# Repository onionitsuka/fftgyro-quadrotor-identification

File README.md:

# FFTGYRO quadrotor identification and SITL

三軸姿勢試験台 FFT GYRO を用いたクアッドロータの荷重・推進応答の同定と、
同定モデルを使ったオフラインシミュレーション／PX4 SITL の研究コードです。

解析・同定、収録用ツール、マイコン／Raspberry Pi の実装、PX4 パッチを収録しています。
実験ログ、解析入力 bundle、第三者のソースツリーは含みません。
**データなしで実行できる例は `sim/appendix/`、論文解析の入口は `analysis.py` です。**

## はじめに

Python 3.11 以上を使い、このリポジトリのルートで実行してください。

```sh
python3 -m venv .venv
.venv/bin/python -m pip install -e '.[analysis,hardware,dev]'
.venv/bin/python -m pytest -q
```

Windows PowerShell では最初のコマンドを `py -3 -m venv .venv`、
以降の `.venv/bin/python` を `.\.venv\Scripts\python.exe` に置き換えてください。
Python の数値処理だけなら `hardware` は不要です。全テストには収録系の依存も使います。
PX4・Gazebo・C++ のビルド環境は Python パッケージに含まれません。
対象と既知の制約は [検証範囲](docs/TESTING.md) を参照してください。

## 入口と再現できる範囲

| やりたいこと | 入口 | 追加で必要なもの |
| --- | --- | --- |
| 保存済み係数で飛行例を計算する | [sim/appendix/](sim/appendix/README.md) | Python 依存のみ |
| 荷重を再構成し、モデルを同定・評価する | [analysis.py](analysis.py) | 実験入力 bundle |
| 保存済み結果から図・表を出す | [analysis_output.py](analysis_output.py) | 解析結果ディレクトリ |
| 現用の荷重モデルを PX4 と組み合わせる | [scripts/run_current_px4_sitl.py](scripts/run_current_px4_sitl.py) | 外部 PX4 ビルド、同定係数・機体設定 |
| Gazebo の機体を使う比較を行う | [scripts/run_native_gazebo_sitl.py](scripts/run_native_gazebo_sitl.py) | 外部 PX4/Gazebo、モデル成果物 |
| 収録・同期処理を読む | [src/fftgyro_quad_id/](src/fftgyro_quad_id/) | 実機運用には装置固有の構成が必要 |

付録シミュレーターは共通の簡易制御器を使います。PX4 SITL や実飛行の再現とは別の計算例です。
MoCap の記録飛行を使う過去の採用版比較は、外部の凍結実行環境とログを必要とするため収録していません。

## データなしで試す

```sh
.venv/bin/python sim/appendix/simulate.py --output sim/appendix/results/example
.venv/bin/python sim/appendix/simulate.py --output sim/appendix/results/example --plot-only
```

比較図は `sim/appendix/results/example/comparison.png` に保存されます。
既存の結果を保つため、再計算時は新しい出力先を指定してください。
ブラウザでの操縦例や Windows の手順は [付録の README](sim/appendix/README.md) を参照してください。

## 解析・同定

入力 bundle を用意した場合の例です。入力形式は [解析入力と出力](docs/ANALYSIS.md) に記載しています。
実験データは配布していないため、このコマンドだけで論文の数値結果を再現することはできません。

```sh
.venv/bin/python analysis.py --bundle /path/to/input-bundle --output output/analysis
.venv/bin/python analysis_output.py --input output/analysis --output output/report
```

`--refit` で保存済み構造に対する係数再推定、`--six-axis --refit` で追加 3 軸を含む
同定・評価を実行します。項の再選択や感度解析は明示的なオプションです。
図・表だけを変更する場合は `analysis_output.py` だけを実行してください。

## コードの構成

| パス | 内容 |
| --- | --- |
| `analysis.py`, `analysis_search.py` | 再構成、回帰、候補探索、誤差計算 |
| `analysis_output.py` | 保存済み結果から図・表を出力 |
| `src/fftgyro_quad_id/` | 同期、座標変換、同定、装置通信などの共通実装 |
| `scripts/` | 現行の起動処理とその依存23ファイル。[入口一覧](scripts/README.md) |
| `tests/` | 合成信号、数式の不変条件、通信モック等を使うテスト |
| `configs/` | 設定例とテスト・実装が参照する条件。区分は [設定の扱い](docs/CONFIGURATIONS.md) を参照 |
| `sim/appendix/` | 保存済み係数による単独シミュレーター |
| `onboard_executor/`, `firmware/`, `hardware/` | Pi 実行系、マイコンのコード、回路設計 |
| `protocol/`, `patches/px4/` | MAVLink 定義と外部 PX4 へ適用するパッチ |

既存の import・パス参照を保つため、研究用コードのフォルダ名は維持しています。
`analysis.py` から読み始め、SITL は [スクリプトの入口](scripts/README.md) を参照してください。

## 先行研究

モデルの項選択には、Sun et al.（2019）の前進・後退ステップワイズ回帰を用いています。
F検定の閾値とPSEによる停止条件は、著者らの公開MATLAB実装を参照し、Pythonで計算しています。

- [Sun, de Visser, and Chu (2019), Quadrotor Gray-Box Model Identification from High-Speed Flight Data](https://doi.org/10.2514/1.C035135)
- [著者らのMATLAB参照実装（固定コミット）](https://github.com/SihaoSun/stepwise_regression/tree/b04095ccb9f0e5dcafae43db6ec1a4320cbd0b16/func)

## 比較条件と解釈

- 実験の物理モデル比較は、実測 RPM がある同一標本で行います。欠測を推算 RPM で補いません。
- `measured` と `command_route` は学習・予測で使う RPM の経路です。推算経路の fit に実測 RPM を混ぜません。
- シミュレーション中の RPM は生成値です。実測 RPM と区別してください。
- 全学習データへの一致と条件別検証を分け、独立停止基準とモデル補助基準を分けます。
- 試験台上の荷重一致だけで自由飛行の精度を保証しません。RTS やゼロ位相フィルタはオフライン処理です。

## ライセンスと外部依存

プロジェクト全体のライセンスは未設定です。
外部依存は [docs/DEPENDENCIES.md](docs/DEPENDENCIES.md)、
第三者由来部分の出典とライセンスは [THIRD_PARTY.md](THIRD_PARTY.md) を参照してください。

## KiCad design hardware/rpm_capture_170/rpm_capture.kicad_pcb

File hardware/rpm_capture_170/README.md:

# RPM capture board

KiCad の回路・基板設計と、配置・経路・組立図を生成する補助コードです。
`rpm_capture.kicad_pro` を KiCad で開いてください。

- 設計ソース：`rpm_capture.kicad_sch`、`rpm_capture.kicad_pcb`、`RPM.kicad_sym`。
- 配置情報：`layout.json`。`previous_layout.json` は比較検証に使う前の配置です。
- 生成・検査：`layout_work.py`、`refine_routes.py`、`make_schematic.py`、`verify_and_render.py`、`make_guide.py`。
- SPICE 計算：`receiver_demo.cir`、`run_simulation.py`。
- 図と検査記録：SVG、組立図 HTML、`verification.json`、`erc.rpt`。

生成スクリプトはこのフォルダ内の設計・出力を更新するため、試す場合はコピーを使ってください。
Python の通常テストには含めていません。KiCad／SPICE と描画の実行環境は別途必要です。

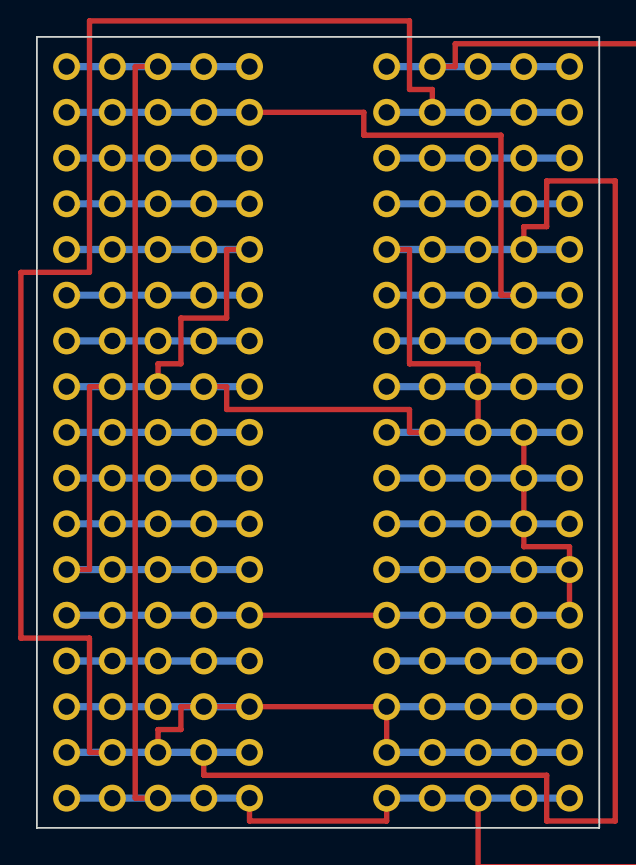
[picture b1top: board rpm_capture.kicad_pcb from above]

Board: 2 copper layers, 31.2 x 43.9 mm, 170 parts (0 on the bottom side), 21 nets.

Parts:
A1: A1
A2: A2
A3: A3
A4: A4
A5: A5
A6: A6
A7: A7
A8: A8
A9: A9
A10: A10
A11: A11
A12: A12
A13: A13
A14: A14
A15: A15
A16: A16
A17: A17
B1: B1
B2: B2
B3: B3
B4: B4
B5: B5
B6: B6
B7: B7
B8: B8
B9: B9
B10: B10
B11: B11
B12: B12
B13: B13
B14: B14
B15: B15
B16: B16
B17: B17
C1: C1
C2: C2
C3: C3
C4: C4
C5: C5
C6: C6
C7: C7
C8: C8
C9: C9
C10: C10
C11: C11
C12: C12
C13: C13
C14: C14
C15: C15
C16: C16
C17: C17
D1: D1
D2: D2
D3: D3
D4: D4
D5: D5
D6: D6
D7: D7
D8: D8
D9: D9
D10: D10
D11: D11
D12: D12
D13: D13
D14: D14
D15: D15
D16: D16
D17: D17
E1: E1
E2: E2
E3: E3
E4: E4
E5: E5
E6: E6
E7: E7
E8: E8
E9: E9
E10: E10
E11: E11
E12: E12
E13: E13
E14: E14
E15: E15
E16: E16
E17: E17
F1: F1
F2: F2
F3: F3
F4: F4
F5: F5
F6: F6
F7: F7
F8: F8
F9: F9
F10: F10
F11: F11
F12: F12
F13: F13
F14: F14
F15: F15
F16: F16
F17: F17
G1: G1
G2: G2
G3: G3
G4: G4
G5: G5
G6: G6
G7: G7
G8: G8
G9: G9
G10: G10
G11: G11
G12: G12
G13: G13
G14: G14
G15: G15
G16: G16
G17: G17
H1: H1
H2: H2
H3: H3
H4: H4
H5: H5
H6: H6
H7: H7
H8: H8
H9: H9
H10: H10
H11: H11
H12: H12
H13: H13
H14: H14
H15: H15
H16: H16
H17: H17
I1: I1
I2: I2
I3: I3
I4: I4
I5: I5
I6: I6
I7: I7
I8: I8
I9: I9
I10: I10
I11: I11
I12: I12
I13: I13
I14: I14
I15: I15
I16: I16
I17: I17
J1: J1
J2: J2
J3: J3
J4: J4
J5: J5
J6: J6
J7: J7
J8: J8
J9: J9
J10: J10
J11: J11
J12: J12
J13: J13
J14: J14
J15: J15
J16: J16
J17: J17

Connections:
D2: A4.1, B4.1, C4.1, D4.1, E4.1
D3: A15.1, B15.1, C15.1, D15.1, E15.1
D4: F4.1, G4.1, H4.1, I4.1, J4.1
D5: F15.1, G15.1, H15.1, I15.1, J15.1
GND: A5.1, A8.1, A12.1, A13.1, A16.1, B5.1, B8.1, B12.1, B13.1, B16.1, C5.1, C8.1, C12.1, C13.1, C16.1, D5.1, D8.1, D12.1, D13.1, D16.1, E5.1, E8.1, E12.1, E13.1, E16.1, F2.1, F5.1, F9.1, F13.1, F16.1, G2.1, G5.1, G9.1, G13.1, G16.1, H2.1, H5.1, H9.1, H13.1, H16.1, I2.1, I5.1, I9.1, I13.1, I16.1, J2.1, J5.1, J9.1, J13.1, J16.1
IN1: A6.1, B6.1, C6.1, D6.1, E6.1
IN2: A10.1, B10.1, C10.1, D10.1, E10.1
IN3: F7.1, G7.1, H7.1, I7.1, J7.1
IN4: F11.1, G11.1, H11.1, I11.1, J11.1
L9: A9.1, B9.1, C9.1, D9.1, E9.1
OUT1: A7.1, B7.1, C7.1, D7.1, E7.1
OUT2: A11.1, B11.1, C11.1, D11.1, E11.1
OUT3: F8.1, G8.1, H8.1, I8.1, J8.1
OUT4: F12.1, G12.1, H12.1, I12.1, J12.1
R10: F10.1, G10.1, H10.1, I10.1, J10.1
RAW1: A3.1, B3.1, C3.1, D3.1, E3.1
RAW2: A14.1, B14.1, C14.1, D14.1, E14.1
RAW3: F3.1, G3.1, H3.1, I3.1, J3.1
RAW4: F14.1, G14.1, H14.1, I14.1, J14.1
SENSOR_5V: A1.1, A17.1, B1.1, B17.1, C1.1, C17.1, D1.1, D17.1, E1.1, E17.1, F1.1, F17.1, G1.1, G17.1, H1.1, H17.1, I1.1, I17.1, J1.1, J17.1
USB_5V: A2.1, B2.1, C2.1, D2.1, E2.1, F6.1, G6.1, H6.1, I6.1, J6.1
